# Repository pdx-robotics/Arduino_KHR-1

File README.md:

# KHR-1 With Arduino
The KHR-1 is made by Kondo Kagaku (近藤科学).

It will be modified to work with a Bluetooth module and an Arduino Board.

## KHR-1 Hardware:
- Servos: KRS-784 ICS
- Servo Control Board: RCB-1

We will not be using the RCB-1 for this project. Servo Control will be done by Arduino

****
## Servo Mapping
The Servos are mapped for reference as seen below:

| Part | Left | Right|
|----|:-----:|:----:|
| Shoulder Pitch |   0   |  15   |
| Shoulder Roll  |   1   |  14   |
| Elbow          |   2   |  13   |
| Hip Roll       |   3   |  12   |
| Hip Pitch      |   4   |  11   |
| Knee           |   5   |  10   |
| Ankle Pitch    |   6   |   9   |
| Ankle Roll     |   7   |   8   |
| Head Pan       |  ???  |

### Part Terminology

#### Pitch and Roll
The terminology of "pitch" and "roll" is used to describe the different axes
that an aircraft in flight can freely rotate about. Here we take advantage of
these names to help us describe the movements of a single joint made up of many servos/motors.

##### Pitch:
- Aircraft: nose up or down about an axis from wing to wing
- Humanoid: face up or down about an axis from hand to hand (see image above)

##### Roll:
- Aircraft: rotation about an axis running from nose to tail
- Humanoid: rotation about an axis running from front to back 

##### Yaw: (not needed for KHR-1)
- Aircraft: nose left or right about an axis running up and down
- Humanoid: face left or right about an axis running up and down

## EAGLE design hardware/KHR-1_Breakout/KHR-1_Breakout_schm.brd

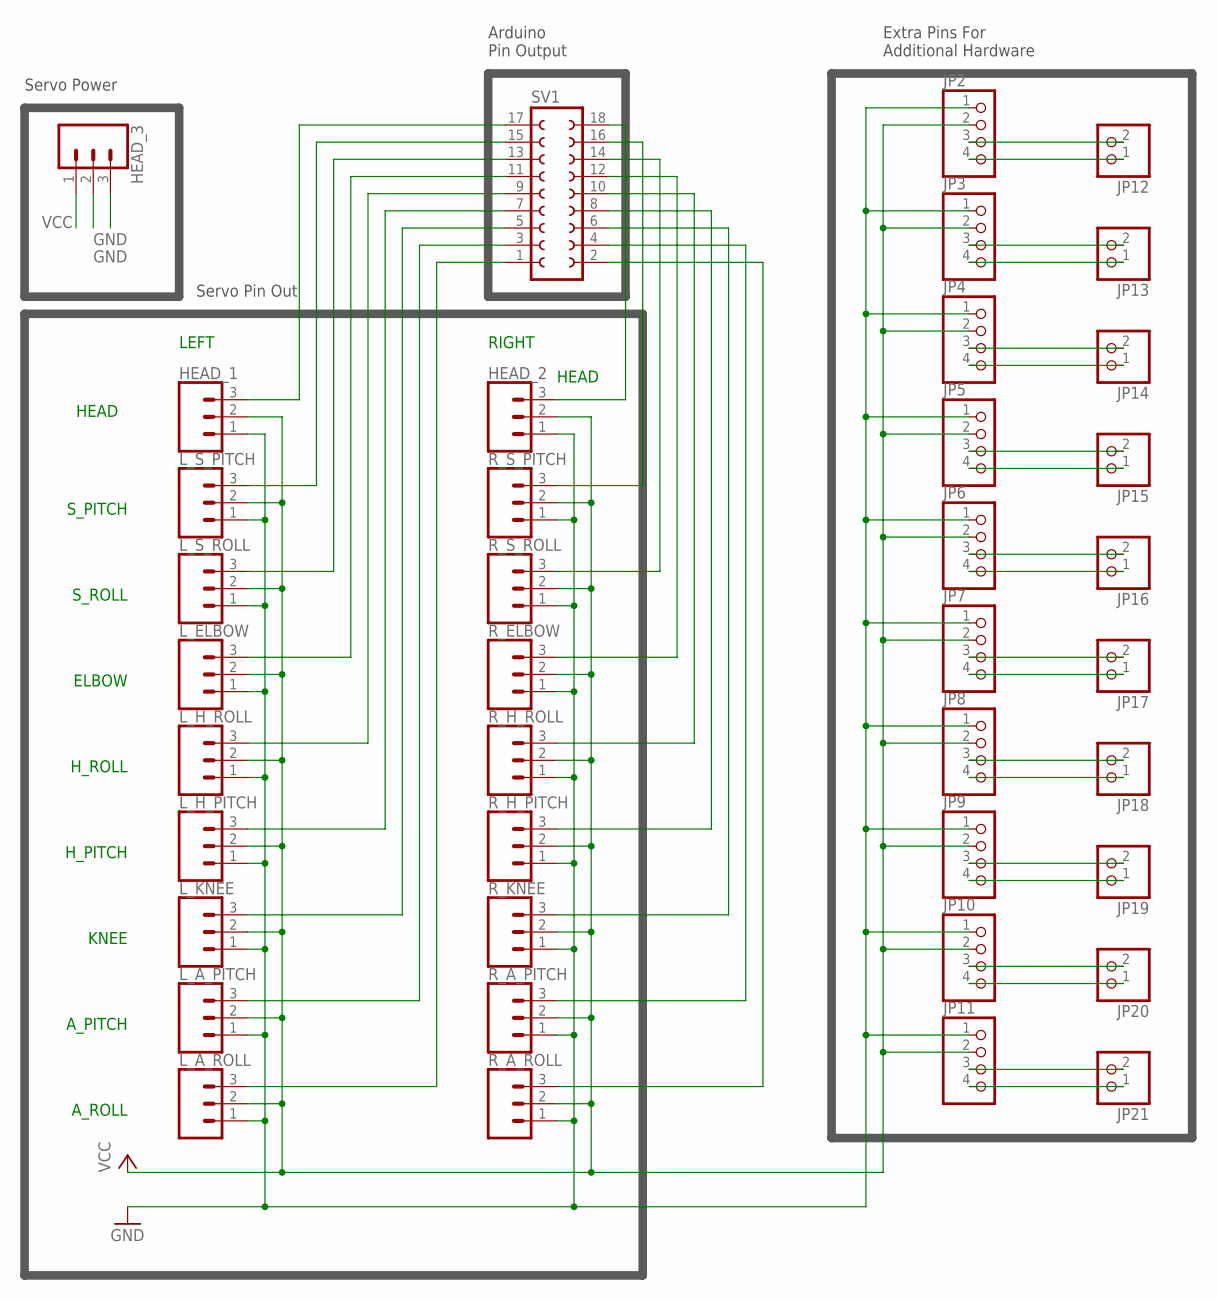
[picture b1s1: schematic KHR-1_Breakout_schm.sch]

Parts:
HEAD_1, HEAD_2, HEAD_3: CONN_03; 1X03
JP2, JP3, JP4, JP5, JP6, JP7, JP8, JP9, JP10, JP11: PINHD-1X4; 1X04
JP12, JP13, JP14, JP15, JP16, JP17, JP18, JP19, JP20, JP21: PINHD-1X2; 1X02
L_A_PITCH: CONN_03; 1X03
L_A_ROLL: CONN_03; 1X03
L_ELBOW: CONN_03; 1X03
L_H_PITCH: CONN_03; 1X03
L_H_ROLL: CONN_03; 1X03
L_KNEE: CONN_03; 1X03
L_S_PITCH: CONN_03; 1X03
L_S_ROLL: CONN_03; 1X03
R_A_PITCH: CONN_03; 1X03
R_A_ROLL: CONN_03; 1X03
R_ELBOW: CONN_03; 1X03
R_H_PITCH: CONN_03; 1X03
R_H_ROLL: CONN_03; 1X03
R_KNEE: CONN_03; 1X03
R_S_PITCH: CONN_03; 1X03
R_S_ROLL: CONN_03; 1X03
SV1: FE09-2

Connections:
GND: HEAD_1.1, HEAD_2.1, HEAD_3.2, HEAD_3.3, JP2.1, JP3.1, JP4.1, JP5.1, JP6.1, JP7.1, JP8.1, JP9.1, JP10.1, JP11.1, L_A_PITCH.1, L_A_ROLL.1, L_ELBOW.1, L_H_PITCH.1, L_H_ROLL.1, L_KNEE.1, L_S_PITCH.1, L_S_ROLL.1, R_A_PITCH.1, R_A_ROLL.1, R_ELBOW.1, R_H_PITCH.1, R_H_ROLL.1, R_KNEE.1, R_S_PITCH.1, R_S_ROLL.1
unnamed: HEAD_1.3, SV1.17
unnamed: L_S_PITCH.3, SV1.15
unnamed: L_S_ROLL.3, SV1.13
unnamed: L_ELBOW.3, SV1.11
unnamed: L_H_ROLL.3, SV1.9
unnamed: L_H_PITCH.3, SV1.7
unnamed: L_KNEE.3, SV1.5
unnamed: L_A_PITCH.3, SV1.3
unnamed: L_A_ROLL.3, SV1.1
unnamed: HEAD_2.3, SV1.18
unnamed: R_S_PITCH.3, SV1.16
unnamed: R_S_ROLL.3, SV1.14
unnamed: R_ELBOW.3, SV1.12
unnamed: R_H_ROLL.3, SV1.10
unnamed: R_H_PITCH.3, SV1.8
unnamed: R_KNEE.3, SV1.6
unnamed: R_A_PITCH.3, SV1.4
unnamed: R_A_ROLL.3, SV1.2
unnamed: JP2.3, JP12.2
unnamed: JP2.4, JP12.1
unnamed: JP3.3, JP13.2
unnamed: JP3.4, JP13.1
unnamed: JP4.3, JP14.2
unnamed: JP4.4, JP14.1
unnamed: JP5.3, JP15.2
unnamed: JP5.4, JP15.1
unnamed: JP6.3, JP16.2
unnamed: JP6.4, JP16.1
unnamed: JP7.3, JP17.2
unnamed: JP7.4, JP17.1
unnamed: JP8.3, JP18.2
unnamed: JP8.4, JP18.1
unnamed: JP9.3, JP19.2
unnamed: JP9.4, JP19.1
unnamed: JP10.3, JP20.2
unnamed: JP10.4, JP20.1
unnamed: JP11.3, JP21.2
unnamed: JP11.4, JP21.1
VCC: HEAD_1.2, HEAD_2.2, HEAD_3.1, JP2.2, JP3.2, JP4.2, JP5.2, JP6.2, JP7.2, JP8.2, JP9.2, JP10.2, JP11.2, L_A_PITCH.2, L_A_ROLL.2, L_ELBOW.2, L_H_PITCH.2, L_H_ROLL.2, L_KNEE.2, L_S_PITCH.2, L_S_ROLL.2, R_A_PITCH.2, R_A_ROLL.2, R_ELBOW.2, R_H_PITCH.2, R_H_ROLL.2, R_KNEE.2, R_S_PITCH.2, R_S_ROLL.2

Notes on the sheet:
LEFT
RIGHT
S_PITCH
S_ROLL
ELBOW
H_ROLL
H_PITCH
KNEE
A_PITCH
A_ROLL
HEAD
Extra Pins For Additional Hardware
Arduino Pin Output
Servo Power
Servo Pin Out

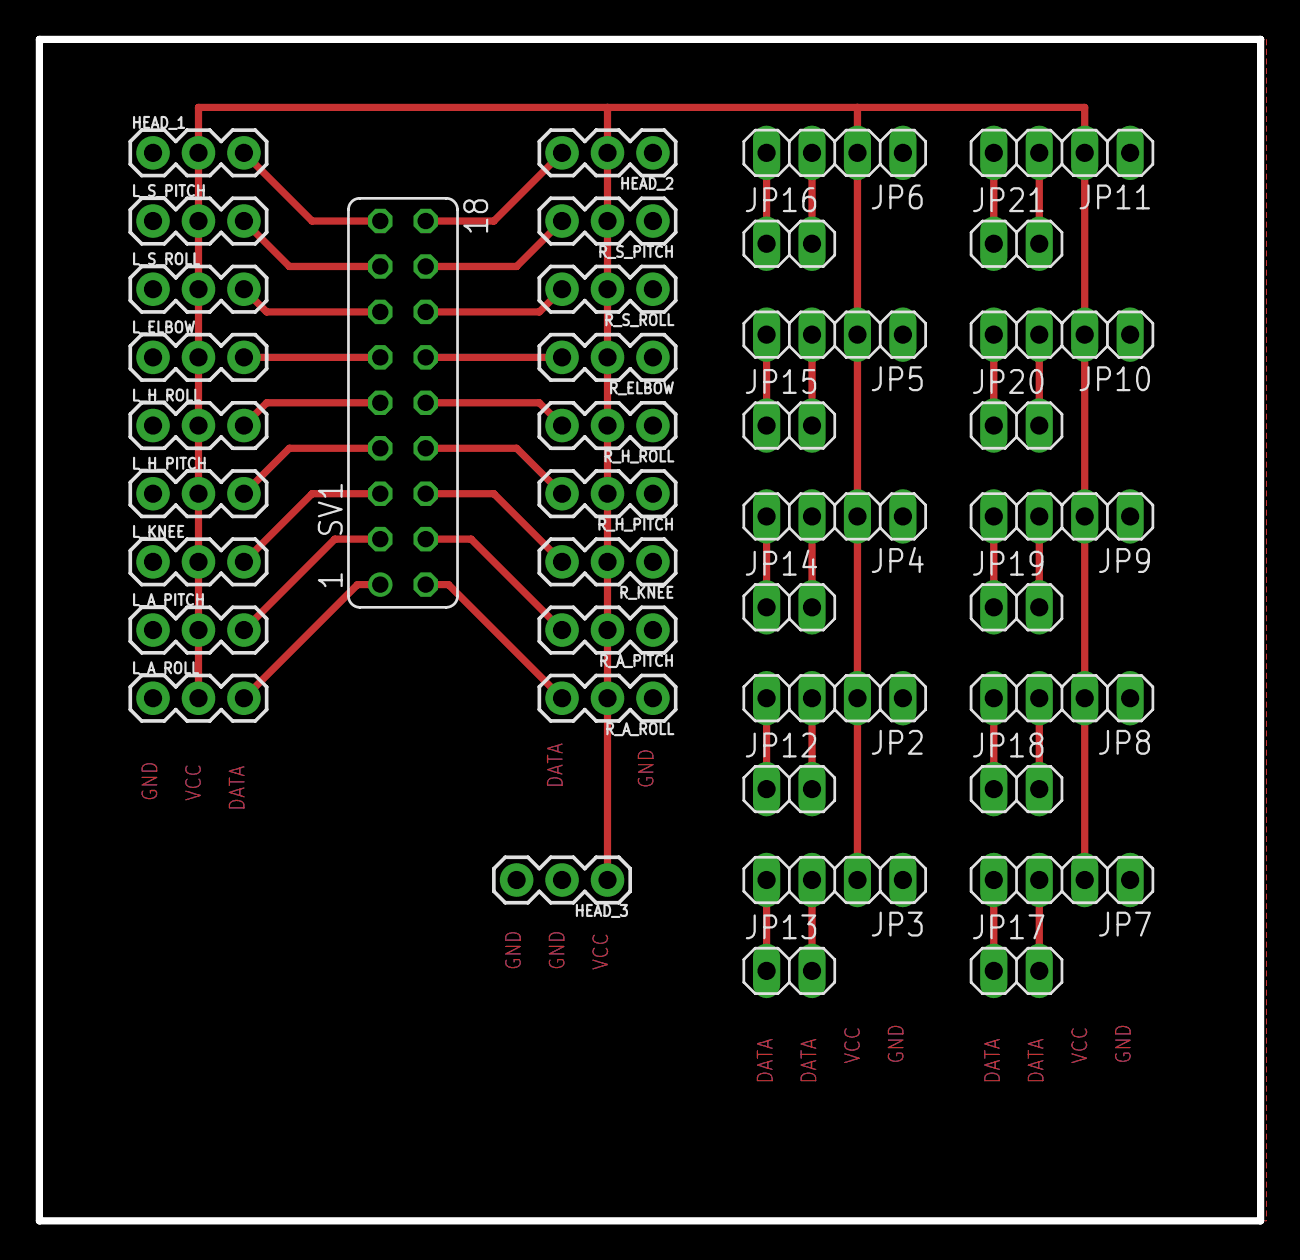
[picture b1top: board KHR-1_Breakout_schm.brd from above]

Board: 2 copper layers, 68.2 x 66.0 mm, 40 parts (0 on the bottom side), 40 nets.

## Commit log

2018-04-07 Push reference documentation and one test program
2018-04-07 Table of Servo names in README
2018-04-07 Add part terminology in README
2018-04-07 Adjust some formating in README
2018-04-07 Adjust formatting for README
2018-04-07 Adjust formatting of README
2018-04-07 Adjust formatting in README
2018-04-28 Added working library for KHR-1
2018-04-28 Git push demo
2018-04-28 Demo with Vim
2018-04-29 Library folder now lib and include serialwrite_servo
2018-05-09 Remove text files and add example program
2018-05-12 add both_wave function
2018-05-16 Format
2018-05-17 Format
    Autoformatted by VSCode
2018-05-17 WIP Add lookup table
    Choosing std::unordered_map for its constant time searching.
    Needs coordinates.
2018-05-18 Fix name
2018-05-19 WIP Add semaphore functions
    - Bundle everything in a class
    - Just read the style guide, changing spaces back to tabs
    - Add untested functions and lookup table
2018-05-20 WIP Change lookup solution, add posing functions
    Well, at least it compiles now...
    - Switch to a non-STL solution for looking up ArmPoses since Arduino doesn't support STL
    - Use a uClibc++ library ported for Arduino. Install it here: https://github.com/maniacbug/StandardCplusplus
    - Move attach() and detach() to constructor and destructor since it makes sense, maybe
    - Still need coordinates for the lookup function
    - Not sure what all the extern VarSpeedServos and then declaring them in the cpp is for, but let's just see if commenting them all out works
2018-05-20 Fix missing return statement
2018-05-24 WIP Add pose coordinates
    - Add dummy poses for testing purposes
    - Move the semaphore function call to its own .ino file
    - Getting rid of the externs seem to work just fine
    - Remove comments
    - Still need coordinates
2018-05-30 Move KHR_1 setup functions to public
    Moved KHR_1::attach() to public so that Arduino setup() can call it directly. It seems that attach() relies on variables that may not have been initialized yet since the KHR_1 constructor is called i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
    Let's see if this fixes everything.
    Issue: https://github.com/pdx-robotics/Arduino_KHR-1/issues/3
2018-05-31 Remove attach() call in constructor
    Removing attach() in the constructor since it was throwing some errors, making later attach() calls no longer work.
    It's finally moving as expected.
    Issue: https://github.com/pdx-robotics/Arduino_KHR-1/issues/3
2018-06-03 Added WIP Servo Direction Map
    Added a text file with a description of how each servo will move given an angle. Very WIP, I added all the data I have right now, and a framework to make adding the rest easier.
    I also plan to add extra data on suggested ranges of motion for mimicking natural human motion, as well as suggestions for which servos should have their directions swapped to make future programming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
2018-06-04 WIP Add semaphore coordinates for letters
    Currently a-d has been tested, e-g is still WIP.
    To get the same servo positions, angles on the left and right need to be supplementary. So 0 on the left would be 180 on the right, which is unintuitive. This could all change because we're planning 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
2018-06-20 WIP Change servo coordinate system
    Added a constructor that translates the prefered coordinates to actual servo coordinates. As of now, a-d are working as expected, but need more testing to confirm.
    Issue: https://github.com/pdx-robotics/Arduino_KHR-1/issues/4
2018-06-24 Rename structs and functions
2018-06-24 Add an argument to pose function
2018-06-24 WIP Implement Animation
    Turned a series of Poses into an Animation.
    Implemented Poses for letters a-n. h & i needed inbetween poses to prevent the arms from getting stuck during movements. They could be moved to an enumToAnimation function together with the semaphore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
    Also fixed some of the coordinates conversion. Letters a-n are working as expected.
    Issue: https://github.com/pdx-robotics/Arduino_KHR-1/issues/4
2018-07-03 WIP Implement Animations
    Added an enum class for semaphore signals that aren't chars. Also added a lookup function for this enum class. Changed the lookup functions to returning Animations instead of Poses.
    When semaphoring a string, KHR_1 now adds in signals at the beginning, end, and when switching from letters to numbers and vice versa. All letters and signals have been implemented. Need more testing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
2018-07-07 added a sweep test for io pin 2-13 using the VarSpeedServo library
2018-07-08 Servo relay board design and gerber files (EPL format)
2018-07-08 Some cleanup and added comments
2018-07-10 tested 17 servos. Check comments for details
2018-07-14 Ok, think I fixed it.
2018-07-17 Modify library to work with servo driver PCA9685
2018-07-18 Optimize semaphore function for memory usage
    KHR_1 can only semaphore short strings because all the animations for every char are appended to a large animation, which is then passed into animate().
    In this commit, semaphore() calls animate() on every little animation, letting it go out of scope and deallocated afterwards.
    The code compiles, but it's untested. Hopefully this will help KHR_1 support longer strings.
2018-07-29 Implement servo control with servo driver PCA9685
2018-07-29 Update diagram for servo driver implementation #12
2018-07-29 Update README servo channel descriptions for issue #12
2018-07-29 Update README to reference new image
2018-07-31 3D model of servo KRS-784 ICS by Jordon
2018-07-31 Move library to lib directory
2018-08-07 Remove comment
2018-08-07 Add leg angles to Pose
    Struct Pose now contains all the angles except head.
    The constructor's argument list has been updated, but there's no standards for conversion yet. Other functions will have to be updated with this new Pose so for now, the code doesn't compile.
2018-08-07 Add leg angles to pose() and animate()
2018-08-11 Create user input sketch for performing semaphore
    This only sketch only writes one character at a time.
2018-08-14 Blueprint for the Servo KRS-784
2018-08-26 Add legs servo conversion
    Moved the conversion from the constructor to pose(). It takes more dynamic memory so we may have to change back later.
    The conversion for the legs seems to be working properly.
    Issue: #4
2018-08-26 Add leg angles to toSemaphoreAnimation()
    Added a basic standing pose. This created a problem where the sketch uses so much memory it can't upload. Will look into fixing this soon.
2018-08-26 Optimize for memory
    Quite obviously, storing small numbers as int was wasting memory. Changed to char. Also VarSpeedServo isn't used anymore so it's removed.
    Link for future reference, https://learn.adafruit.com/memories-of-an-arduino/optimizing-sram
2018-09-08 Fix serial monitor output
    Since I changed Pose's members to char, serial monitor output prints chars instead of numbers. Casting to int fixed the problem.
2018-09-08 Improve serial monitor output
    Added which signal KHR_1 is posing, and whitespace to separate each signal for ease of reading.
    All strings in Serial.print() are now wrapped with F() to save RAM. See reference: https://www.baldengineer.com/arduino-f-macro.html
2018-09-13 Remove VarSpeedServo
2018-09-21 Change delay times
2018-09-21 Add Pose between same letters
    When string contains the same letter twice or more times in a row, adds a pose inbetween to make movements more readable.
2018-09-22 Update servo diagram's url
2018-10-01 Add uppercase letter support
    There will be no distinction between upper and lowercase, but now KHR_1 will semaphore uppercase letter and not freeze up.
2018-10-02 Add option to disable start and end signals
    semaphore() now have an optional parameter to disable "Attention" and "Ready to Receive" signals at the begin and end of the full animation. This is to cut time when you get a little too impatient du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
2018-10-03 Remove macros and move constants into class
    As mentioned in PR https://github.com/pdx-robotics/Arduino_KHR-1/pull/25 I'm changing all the #define macros into static const int and static inline functions. This doesn't take more memory because o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
2018-10-04 PDF drawing for the custom backplate on KHR-1
2018-10-04 Assembly file for KHR-1's back enclosure
    Solidworks Assembly file for KHR-1's custom back enclosure
2018-10-07 Added some documentation in code.
    Added some documentation to the following files, all of which pertain to the rand_wave.ino program.
    /lib/KHR_1.cpp
    /lib/KHR_1.h
    /examples/rand_wave/rand_wave.ino
    Also found a redundant include a statement in /lib/KHR_1.cpp LINE-27 which was commented out.
2018-10-07 Changed the name of some files to match the repo name.
    Changed the name of the following files to match the repo name.
    lib\KHR_1.h -> lib/Arduino_KHR1.h
    lib\KHR_1.cpp -> lib/Arduino_KHR1.cpp
    changed the includes to match the new name of the header file in the following.
    examples\rand_wave\rand_wave.ino LINE-6
2018-10-07 Updated code to match servo diagram.
    Changed the defines in lib/Arduino_KHR1.h to match the servo diagram at the top and the servo reference.
    However, due to the limitations of VarSpeedServo.h the head w of the KHR_1 was set to CH- 8 and the servos below the chest were commented out for the time being.
2018-10-08 Changed the names of some files.
    Changed the names of the following files to match the repo name.
    This is to help resolve the issues #12.
    lib/KHR_1.h -> lib/Arduino_KHR1.h
    lib/KHR_1.cpp -> lib/Arduino_KHR1.cpp
    Updated all files with the renamed .h file.
2018-10-09 Fixed error in the naming of some files.
    Changed the names of the following files and updated all file with the new header file name.
    lib/Arduino_KHR1.h -> lib/Arduion_KHR-1.h
    lib/Arduino_KHR1.cpp -> lib/Arduion_KHR-1.cpp
2018-10-09 Add sketch of pin wirings for KHR1 control board
2018-10-10 Delete outdated files.
    Delete outdated files from repo.
    The files that were deleted is as follows.
    removed - examples/SerialWrite_Servo
    removed - speed_test
    - examples/SerialWrite_Servo used the VarSpeedServo library which is out of date with the hardware of KHR-1 and will not work with the current set up.
    - speed_test also used the VarSpeedServo library, is incompatible with KHR1, and was not constant with the file hierarchy that has been put into place.
2018-10-11 Add inventory list
    There is now a list of all the spare parts for KHR-1.
    file location hardware\KHR-1_Inventory.txt
2018-10-19 Add Pose with all servos set to zero
2018-10-19 Fix typo and whitespace
2018-10-19 Move function definition and variable init out of header
2018-10-22 relocate files into correct folders
2018-10-22 update Solidworks files and drawings
2018-10-23 Change Pose's members order
    Issue: #38
2018-10-23 Add images of schematic and pcb
2018-11-04 Added 4 3D models for a new BackPack
    3D models for a new KHR1 BackPcak.
    There are 4 parts in total.
2018-11-04 Added some Images of the parts
    Added some images of all the parts for the new KHR-1 backpack and some pdf of the part.
2018-11-05 Fix servo channels diagram link in README.md
2018-11-07 Merged all photos and Tech Drawings
    Merged all photos and Tech Drawings relating to the New KHR-1BackPack

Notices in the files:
parts and their libraries:
SparkFun-Connectors: Licensing: Creative Commons ShareAlike 4.0 International - https://creativecommons.org/licenses/by-sa/4.0
